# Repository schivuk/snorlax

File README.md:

# Snorlax
18-549 Embedded Systems Capstone Project

# Instructions
##Running the web app

1. Install the Machine Learning Library scikit-learn: **pip install scikit-learn**
2. From the webapp directory, run: **python manage.py runserver 0.0.0.0:8000**

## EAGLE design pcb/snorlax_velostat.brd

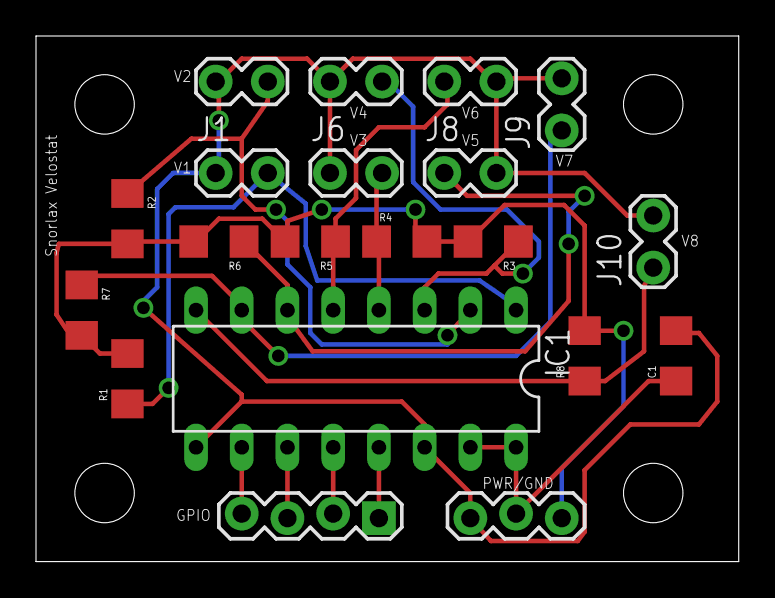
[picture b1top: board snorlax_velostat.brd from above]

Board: 2 copper layers, 39.0 x 29.2 mm, 25 parts (0 on the bottom side), 15 nets.

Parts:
C1: 22uF; 1206
FRAME1: FRAME-LETTER; CREATIVE_COMMONS
H1, H2, H3, H4: STAND-OFF
IC1: MCP3008; DIL16
J1, J2, J3, J6, J7, J8, J9, J10: 1X02_LOCK
J4: 1X03_LOCK
J5: 1X04_LOCK
R1, R2, R3, R4, R5, R6, R7, R8: 500; 1206

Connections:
CH1: IC1.1, J1.2, R1.1
CH2: IC1.2, J2.2, R2.1
CH3: IC1.3, J3.2, R3.1
CH4: IC1.4, J6.2, R4.1
CH5: IC1.5, J7.1, R5.1
CH6: IC1.6, J8.1, R6.1
CH7: IC1.7, J9.1, R7.1
CH8: IC1.8, J10.1, R8.1
GND: C1.2, IC1.9, IC1.14, J1.1, J2.1, J3.1, J4.3, J6.1, J7.2, J8.2, J9.2, J10.2
unnamed: IC1.13, J5.1
unnamed: IC1.12, J5.2
unnamed: IC1.11, J5.3
unnamed: IC1.10, J5.4
VCC_3.3: C1.1, IC1.15, IC1.16, J4.2
VCC_5.5: J4.1, R1.2, R2.2, R3.2, R4.2, R5.2, R6.2, R7.2, R8.2

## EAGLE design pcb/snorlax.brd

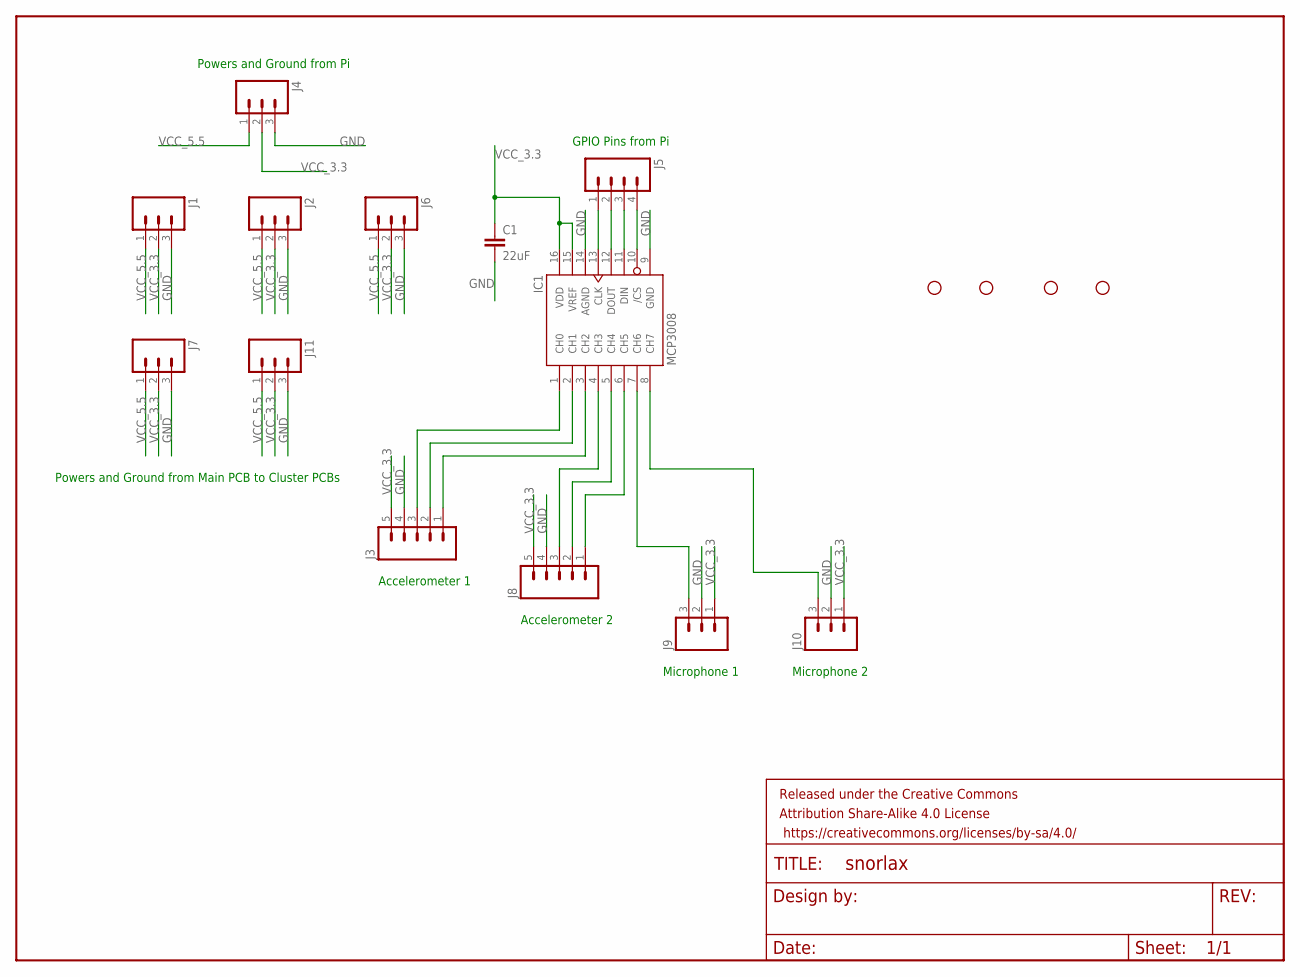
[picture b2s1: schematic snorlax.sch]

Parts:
C1: 22uF; 1206
FRAME1: FRAME-LETTER; CREATIVE_COMMONS
H1, H2, H3, H4: STAND-OFF
IC1: MCP3008; DIL16
J1, J2, J4, J6, J7, J9, J10, J11: M03LOCK; 1X03_LOCK
J3, J8: M05LOCK; 1X05_LOCK
J5: M04LOCK; 1X04_LOCK

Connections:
GND: C1.2, IC1.9 (GND), IC1.14 (AGND), J1.3, J2.3, J3.4, J4.3, J6.3, J7.3, J8.4, J9.2, J10.2, J11.3
unnamed: IC1.1 (CH0), J3.3
unnamed: IC1.2 (CH1), J3.2
unnamed: IC1.3 (CH2), J3.1
unnamed: IC1.4 (CH3), J8.3
unnamed: IC1.5 (CH4), J8.2
unnamed: IC1.6 (CH5), J8.1
unnamed: IC1.7 (CH6), J9.3
unnamed: IC1.8 (CH7), J10.3
unnamed: IC1.13 (CLK), J5.1
unnamed: IC1.12 (DOUT), J5.2
unnamed: IC1.11 (DIN), J5.3
unnamed: IC1.10 (/CS), J5.4
VCC_3.3: C1.1, IC1.15 (VREF), IC1.16 (VDD), J1.2, J2.2, J3.5, J4.2, J6.2, J7.2, J8.5, J9.1, J10.1, J11.2
VCC_5.5: J1.1, J2.1, J4.1, J6.1, J7.1, J11.1

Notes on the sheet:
Accelerometer 1
Accelerometer 2
Microphone 1
Microphone 2
GPIO Pins from Pi
Powers and Ground from Pi
Powers and Ground from Main PCB to Cluster PCBs

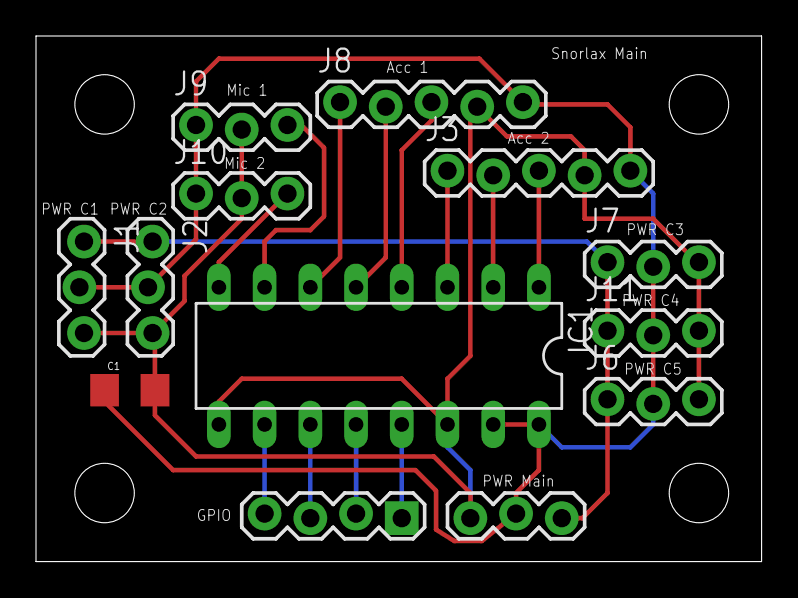
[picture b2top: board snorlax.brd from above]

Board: 2 copper layers, 40.3 x 29.2 mm, 18 parts (0 on the bottom side), 15 nets.

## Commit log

2016-02-16 Initial website
2016-02-16 Almost done
2016-02-16 Add hints for what to do lol
2016-02-16 Add notes for what each section should actually have
2016-02-20 Mostly complete website for checkpoint 1
2016-02-20 Removed team members section and listed at start
2016-02-20 Deleted unnecessary html files
2016-02-28 Initial Django webapp implementation for storing sensor data
2016-02-28 Update gitignore
2016-03-03 Embedded development blog to website
2016-03-21 Added .pyc, .DS_STORE to .gitignore
2016-03-21 Added get request Arduino file
2016-03-21 Added Arduino sketch to find MAC address
2016-04-02 PCB Designs - schematic and board layout
2016-04-02 Add models for accelerometer, velostat, and microphone sensor data
2016-04-04 Added trainPosition view, ReadingGroup and SensorReading classes
2016-04-08 Add architecture diagram to website and TODOs for use cases and interacton diagrams
2016-04-09 Added the base templating for the webapp and added the static dependencies
2016-04-10 Added rawdata.html, routing
2016-04-10 dashboard template
2016-04-10 Removed .pyc files, added /base view
2016-04-10 Fixed the charts and added the dashboard template
2016-04-11 Added the alarm, profile and feedback templates and added the interaction diagram
2016-04-11 Graph peaks
2016-04-11 Initial sleep movement and sleep cycle analysis
2016-04-11 Script to sample fewer points from data
2016-04-12 Deleted sub-directory gitignore and fixed typo in root gitignore
2016-04-12 Removed eagle time interval backups
2016-04-12 Final PCB Schematics, Board Layouts and Gerber Files
2016-04-12 Added url routing for all the links in the dashboad
2016-04-12 Moved the readme file to root
2016-04-13 Fixed the css styles for the templates
2016-04-13 changed the alarm to submit as a form when set or turned off
2016-04-14 Added calendar to log sleep page
2016-04-15 Added alarm backend
2016-04-16 Basic backend and model for logging sleep
2016-04-16 Initial time series graph of sleep cycle with data from text file
2016-04-16 Initial donut chart for sleep cycles
2016-04-16 Fix bug for line chart
2016-04-16 Change parameters for sleep cycle detection
2016-04-17 Added click event for calendar and set defaults for form
2016-04-17 Added backend for log sleep display
2016-04-17 Added hidden input for date in log sleep
2016-04-17 populated the form with the date
2016-04-17 Complete backend for logging sleep and retrieving across dates
2016-04-17 Add REM analysis to algorithm
2016-04-17 REM algorithm for y axis and z axis
2016-04-17 Display REM sleep analysis on web app
2016-04-17 Add seconds to x-axis
2016-04-18 Fixed the form to show the logged sleep data
2016-04-18 Added LogGroups to store most recent velostat readings
2016-04-18 Added sleep-analysis folder for analysis algorithms
2016-04-18 Added .sqlite3 to gitignore
2016-04-18 Sleep data from Sunday night
2016-04-21 Added logging to text files for position data, on-or-off data
2016-04-21 Added events for editing the alarm
    Added the increment and decrements event for the alarm
2016-04-21 Added get request for checking alarm ready
2016-04-21 Fixed the alarm styles and added js functionality
2016-04-22 Added rasPi alarm file (draft)
2016-04-22 Added raspi-with-alarm.py, updated raspi-adc-pot.py
2016-04-22 Changed 'thread' to 'threading'
2016-04-23 Small changes to raspi-with-alarm; changed response type for isAlarmReady view
2016-04-23 Added sleeping position images
2016-04-23 Added resetTraining, trainCurrentPosiion views
2016-04-23 Added train.html
2016-04-23 Added train.js to make AJAX calls for current position
2016-04-24 Logging current position via web app: end-to-end
2016-04-24 Added getNumReadingGroups view
2016-04-24 Added reset all training data feature
2016-04-24 Fixed bugs with front end
2016-04-24 Added getCurrentPosition view
2016-04-24 Added exception catching for 'not enough training samples'
2016-04-24 Added images for sleeping poitions, changed logo to snorlax pic
2016-04-24 Added currposition.js
2016-04-24 Default image is blank
2016-04-24 Added off image
2016-04-25 Added saving to text file after position calibration:
2016-04-25 Added chart to calibration page
2016-04-25 Small changes to train.js
2016-04-25 Updated raspi-with-alarm
2016-04-26 added matlab script to plot trained velostat data
2016-04-26 Added alarm sound playing and check for alarm off
2016-04-26 Alarm is fully functional on webapp now
2016-04-26 Modified view and models to include on/off data
2016-04-26 Added numOnOffSamples
2016-04-26 Added on-off training feature to train.html
2016-04-26 Added number of on-off samples taken to front-end
2016-04-26 added reset for on/off
2016-04-27 Restructured on/off and position related functions for code reuse (writing to files, logging to DB, etc; Added on-off badge on showposition page
2016-04-27 More refactoring (getCurrentPosition)
2016-04-27 Refactored getPosition
2016-04-27 Fixed chart update, added log current as threshold feature
2016-04-27 Added the toggle switches for alarm and the calendar for the dashboard
2016-04-28 Merged the chart configuration with the calendar selection
2016-04-28 Added threshold button, tried to fix chart JS shrinking issue
2016-04-28 Added isOffBed to raspi-alarm file
2016-04-28 Added web backend for sleepp position buzzer toggle
2016-04-28 Added firmware code to buzz sound for forbidden sleeping positions
2016-04-28 Fix bug where charts resize after every ajax call
2016-04-28 Added debug statements in checkOnOff, debugged raspi-with-alarm
2016-04-29 Fixed the chart js issue and updated chart js version
2016-04-29 Add new sleep data
2016-04-29 Restful vs nonrestful sleep analysis
2016-04-29 Add sleep data
2016-04-29 Simplified views.py location buzzer functions
2016-04-29 Sleep efficiency and total time in restful and nonrestful sleep
2016-04-29 Updated raspi-with-alarm: checking for ConnectionError after requests
2016-04-29 Return sleep analysis for specific dates based on calendar selection
2016-04-29 Added error message for no data on dashboard
2016-04-29 Added locks to raspi for requests
2016-04-30 Make x-axis spaced evenly for sleep analysis
2016-04-30 Fixed charts and added more info to dashboard
2016-04-30 Added logging to file for test
2016-04-30 Added thresholding
2016-04-30 Add more sleep data
2016-04-30 Remove purple to red on doughnut chart hover
2016-04-30 Updated alarm file on RPI
2016-04-30 Removed profile page
2016-04-30 Add sleep analysis for today (4/30/2016)
2016-04-30 Fixed bug in feedback form
2016-04-30 All Raspberry Pi server code for sending data, alarms, and buzzer
2016-04-30 Added sleeping position percentage
2016-04-30 Upate caching
2016-04-30 Modified alarm to start playing at second 0
2016-04-30 Added the logSleep object to context
2016-04-30 Fixed issue in views.py
2016-05-01 All sleep data
2016-05-01 Added the dreams panel to the dashboard
2016-05-02 Use HTTPS for Tumblr IFrame
2016-05-10 Added the new website

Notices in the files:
parts and their libraries:
SparkFun-Aesthetics: Licensing: Creative Commons ShareAlike 4.0 International - https://creativecommons.org/licenses/by-sa/4.0
SparkFun-Aesthetics: Released under the Creative Commons Attribution Share-Alike 4.0 License
SparkFun-Aesthetics: https://creativecommons.org/licenses/by-sa/4.0
